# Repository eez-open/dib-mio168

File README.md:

### Ownership and License
The contributors are listed in CONTRIB.TXT.

Licenses | OSHWA UID
--|--
 | 

### Overview

The [EEZ DIB](https://github.com/eez-open/modular-psu) MIO168 module features multiple digital I/O, analog outputs and expansion connectors for carry various AFEs.

### Feature list

* On-board [STM32F446ZCT6](https://www.st.com/content/st_com/en/products/microcontrollers-microprocessors/stm32-32-bit-arm-cortex-mcus/stm32-high-performance-mcus/stm32f4-series/stm32f446/stm32f446zc.html) high-performance foundation line MCU, ARM Cortex-M4 with DSP and FPU, 256 KiB Flash, LQFP-144 package 
* 1 x 8-pin single row 3.81 mm connector (digital inputs)
* 1 x 16-pin dual row 3.81 mm I/O connector (digital and analog outputs)
* 2 x 10-pin ADIB 2.0 mm connectors
* 8 x protected digital inputs (3.3/5/24 V), 2 x fast/slow, 6 x slow
* 8 x digital outputs (low-side) with multiple protections, voltage clamp 42V, current limit 10 A
* 2 x PWM outputs (protected) or sensor bias power (+/-15 V, max. 10 mA)
* 2 x analog bipolar outputs (+/-5 V, +/-10 V, 0-5 V, 0-10 V). Voltage or current output with protection. 12-bit DAC, replaceable with pin compatible 14- or 16-bit version
* 2 x analog bipolar outputs +/-10 V. 12-bit DAC, replaceable with pin compatible 14- or 16-bit version
* On-board isolated power supply with +/-5.3 V outputs (with 4x multipliers), +/-15 V and +3.3 V LDO
* Firmware download via SPI
* Optional SWD for debugging
* I2C EEPROM for storing board specific parameters
* Dimensions: 146 x 95 mm, 4-layer PCB

### r3B1 prototype 3D model (without AFE installed)

### Firmware repository

https://github.com/eez-open/dib-mio168-fw  
The firmware download procedure is described in [Chapter 13.2](https://www.envox.eu/eez-bench-box-3/bb3-user-manual/13-firmware-upgrade/#bb3_man_module_upgrade) of the User Manual.  
The MIO168 module GUI is described in [Chapter 19](https://www.envox.eu/eez-bench-box-3/bb3-user-manual/19-mio168-mixed-input-output-module/) of the User Manual. 

### KiCad project (v7 or newer)

* [MIO168 r3B1](https://github.com/eez-open/dib-mio168/tree/master/EDA%20files/KiCad)

All symbols, footprints and 3D models used in the project can be found in the [EEZ-DIB Library](https://github.com/eez-open/eez-kicad-libraries) plugin for KiCad.

### Bill of materials

* [Download](https://github.com/eez-open/dib-mio168/tree/master/EDA%20files/KiCad/bom/ibom.html) as raw file _Interactive BOM_ (ibom.html) and open it locally in your browser.

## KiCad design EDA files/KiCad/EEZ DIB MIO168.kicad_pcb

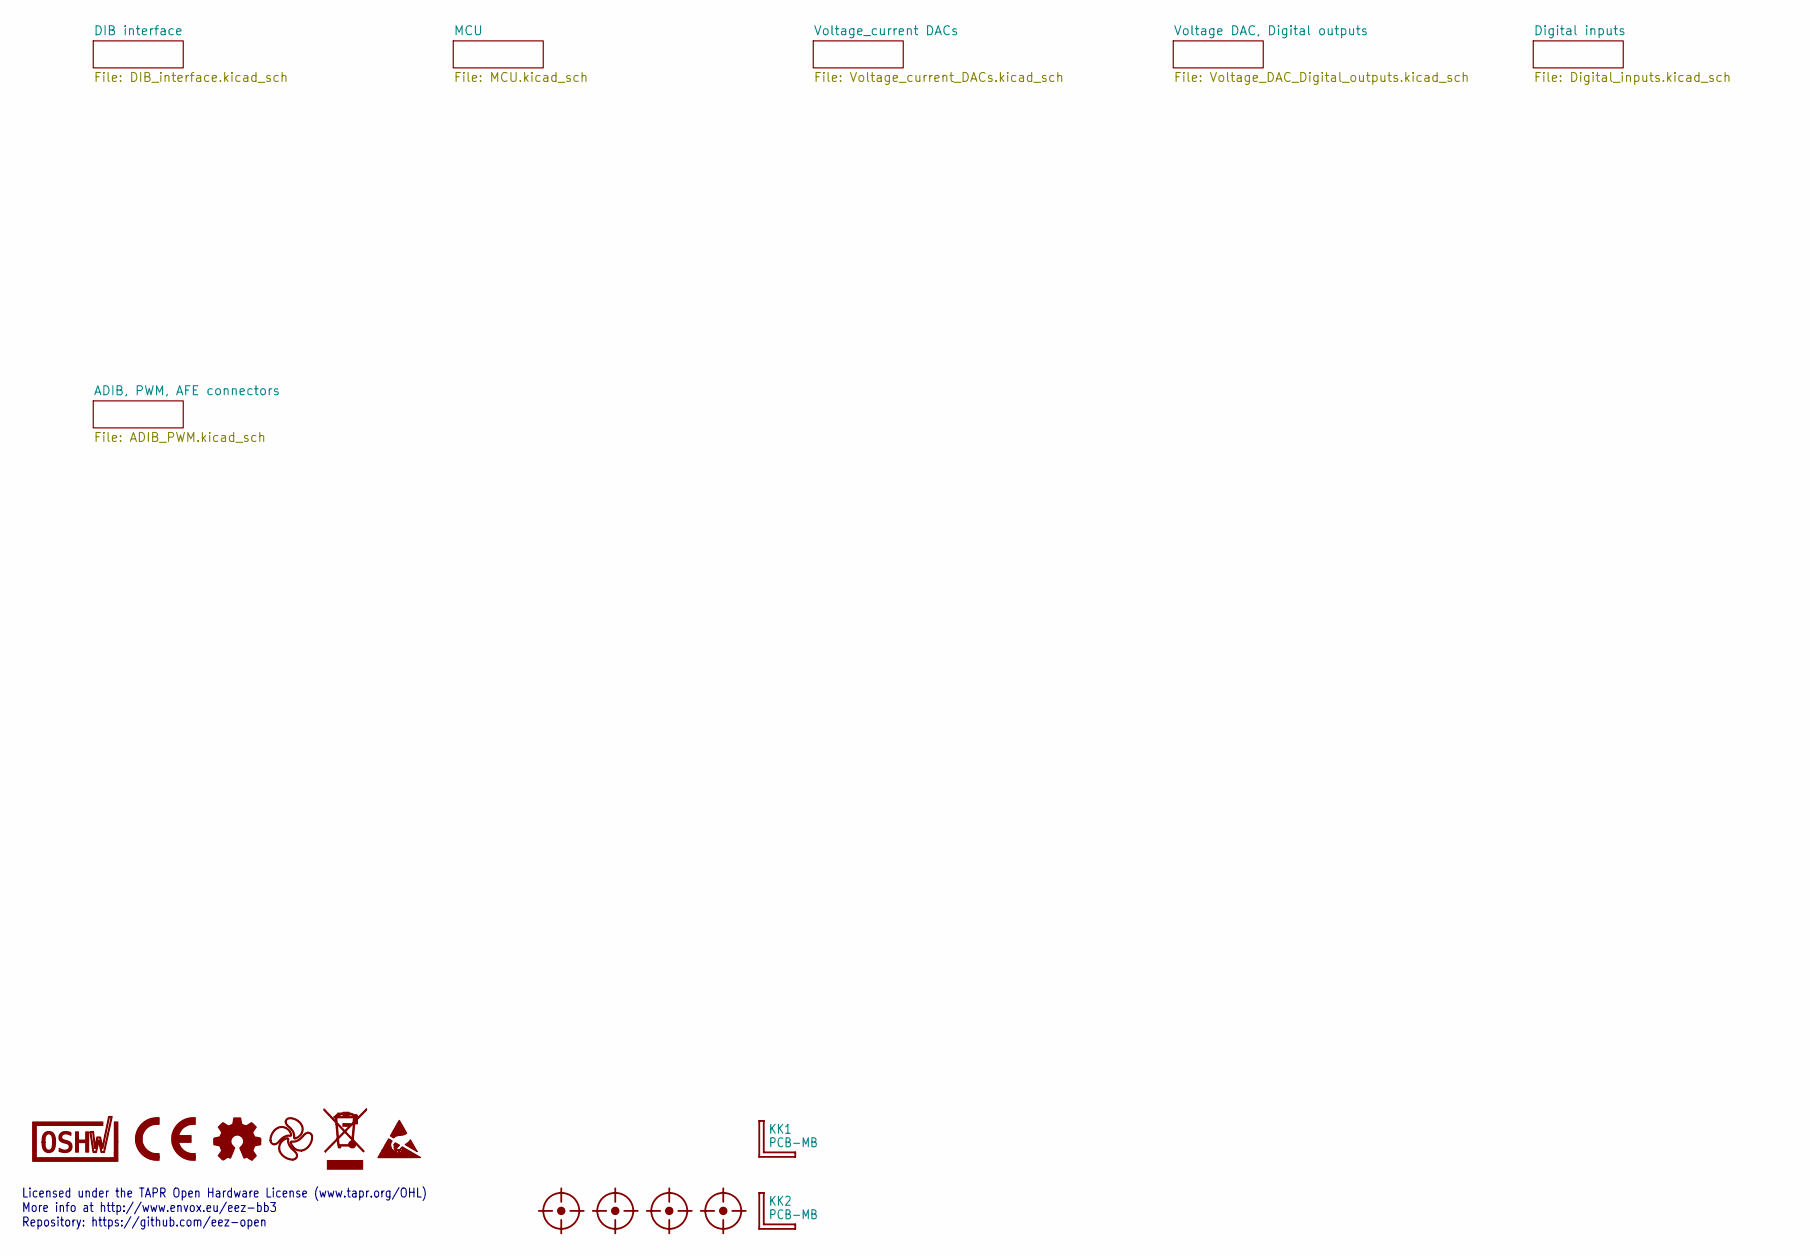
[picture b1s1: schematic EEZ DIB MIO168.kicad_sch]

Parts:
FM1, FM2, FM3, FM4: FIDUCIAL_2; Fiducial
KK1, KK2: PCB-MB; PCB-MB-01; DigiKey RPC1760-ND
LOGO1: OSHWA logo; OSHWA logo (9.5 x 5 mm)
LOGO2: CR logo; CE logo
LOGO3: Open HW logo
LOGO4: EEZ logo; EEZ logo (outline 6mm)
LOGO5: WEEE logo
LOGO6: ESD logo

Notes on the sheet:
Licensed under the TAPR Open Hardware License (www.tapr.org/OHL) More info at http://www.envox.eu/eez-bb3 Repository: https://github.com/eez-open

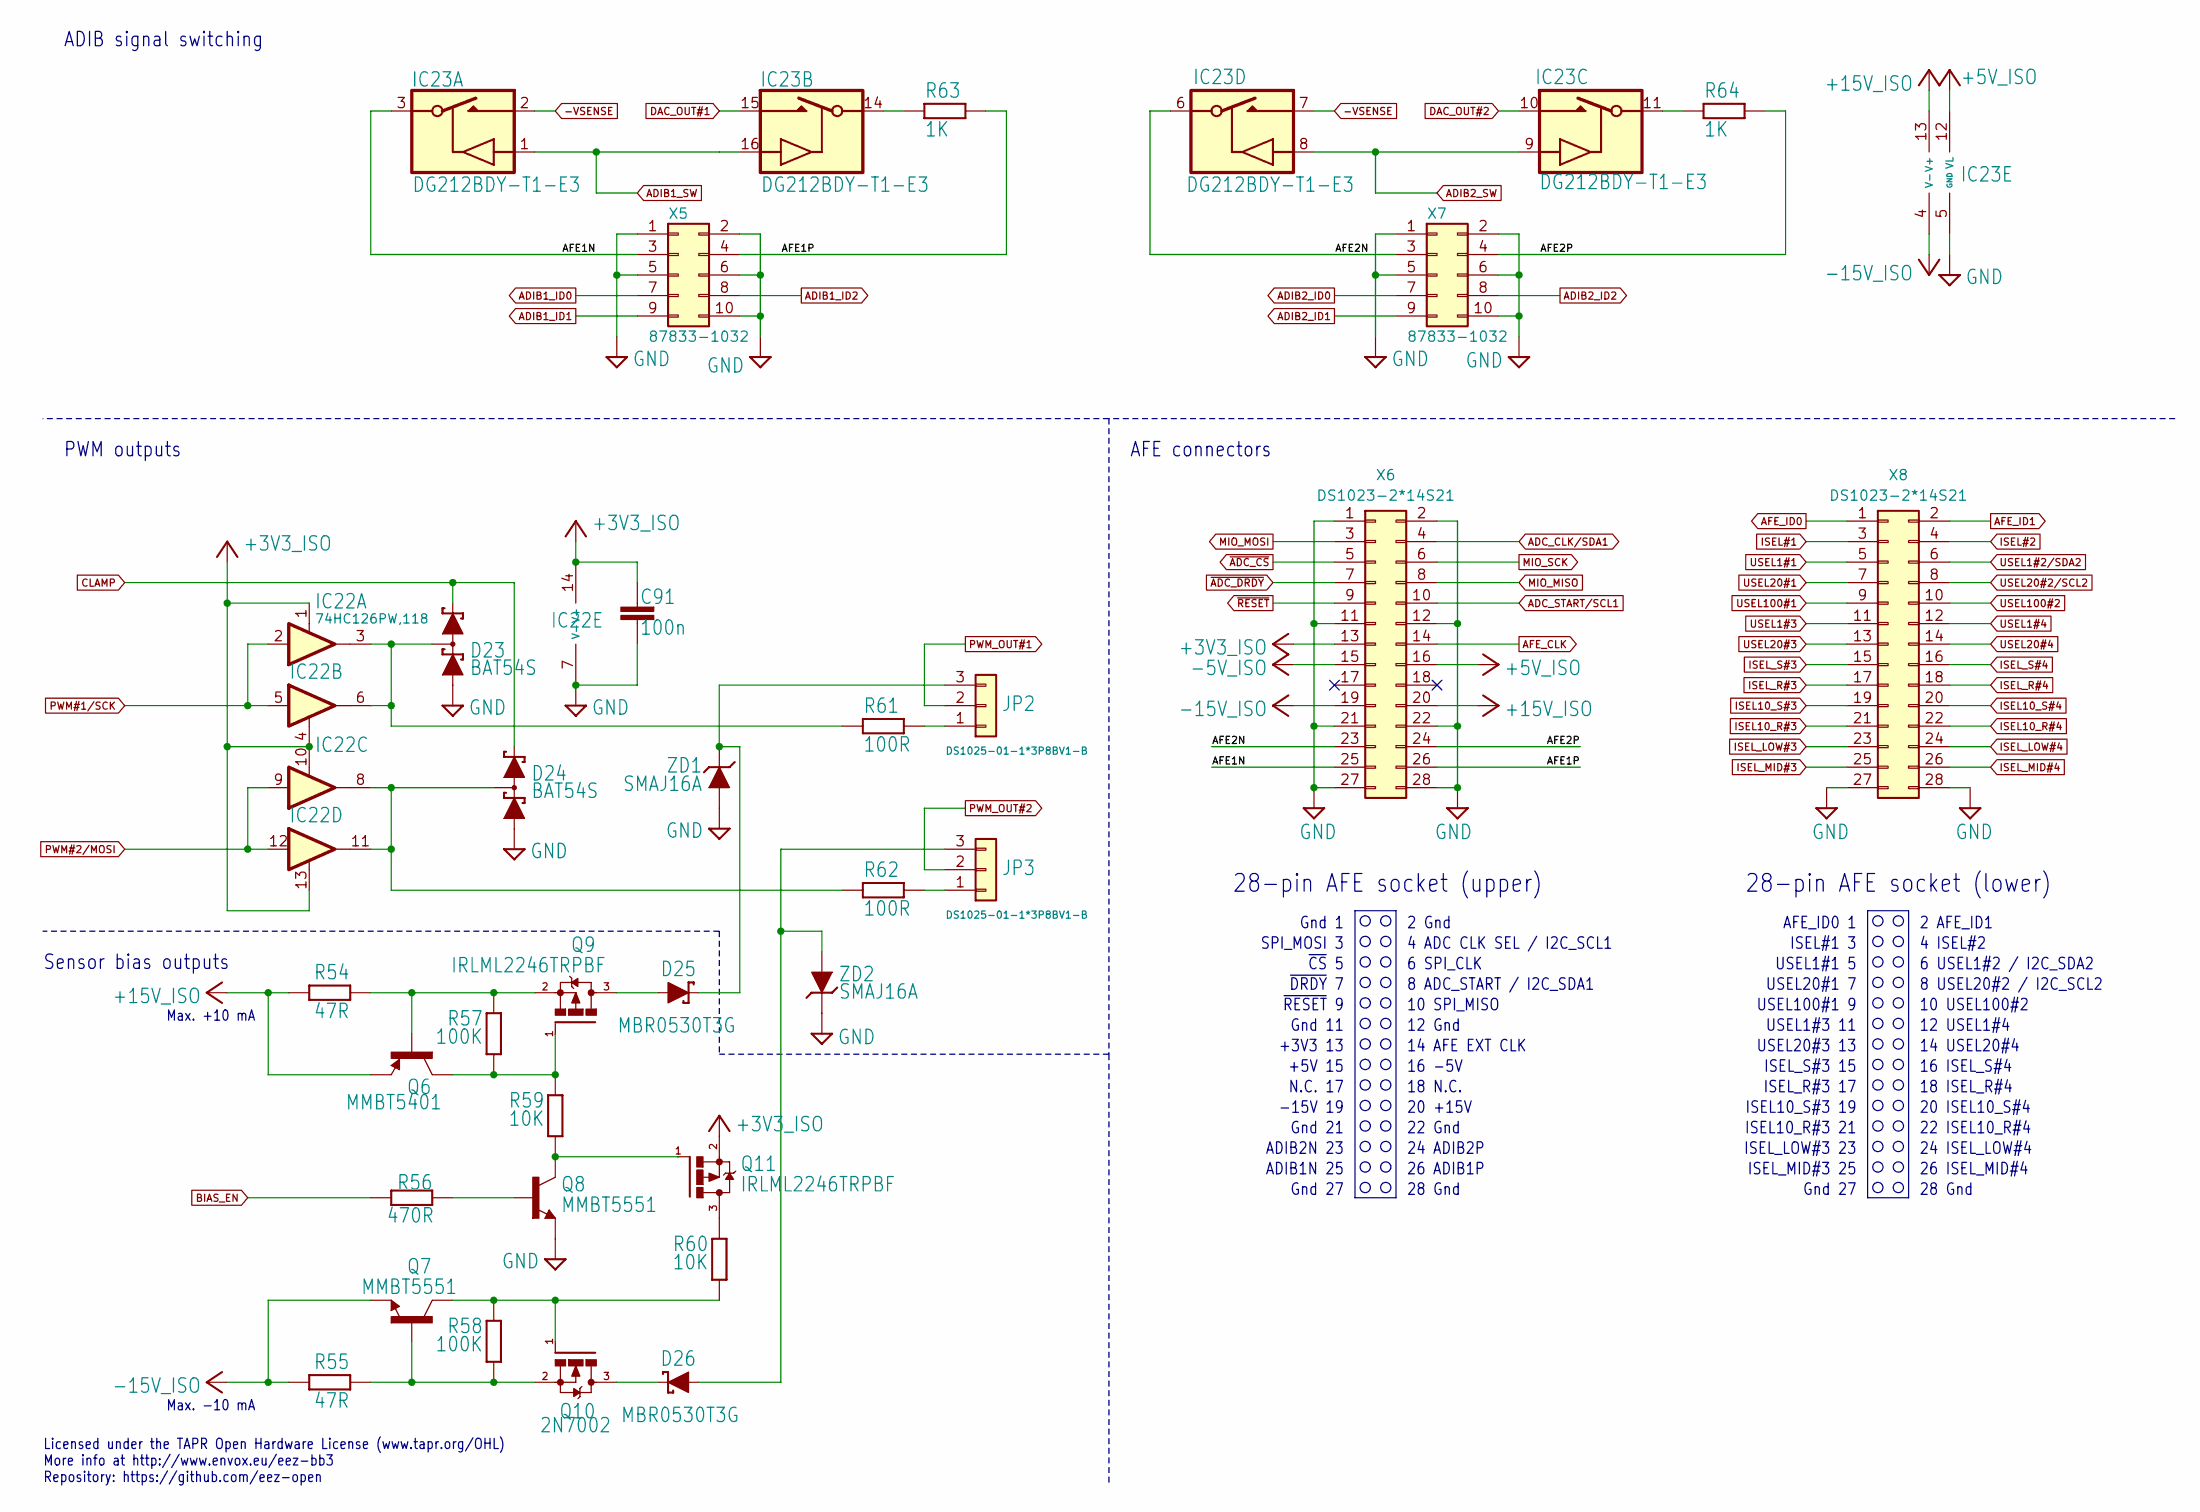
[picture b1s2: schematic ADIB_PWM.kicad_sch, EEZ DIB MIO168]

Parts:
C91: 100n; C_0603_1608Metric; DigiKey 1276-1005-2-ND
D23, D24: BAT54S; SOT23-3; DigiKey 497-2522-1-ND
D25, D26: MBR0530T3G; SOD123; DigiKey 863-MBR0530T3G
IC22: 74HC126PW,118; PW(R-PDSO-G14); DigiKey 1727-6579-1-ND
IC23: DG212BDY-T1-E3; SO16; DigiKey DG212BDY-T1-E3CT-ND
JP2, JP3: DS1025-01-1*3P8BV1-B; ZL303-03P; DigiKey 952-1312-ND
Q6: MMBT5401; SOT23-BEC; DigiKey MMBT5401-FDICT-ND
Q7, Q8: MMBT5551; SOT23-BEC; DigiKey MMBT5551LT1GOSCT-ND
Q9, Q11: IRLML2246TRPBF; SOT103P240X110-3N; DigiKey IRLML2246TRPBFTR-ND
Q10: 2N7002; SOT103P240X110-3N; DigiKey 2N7002LT1GOSCT-ND
R54, R55: 47R; R_0805_2012Metric; DigiKey P47.0CCT-ND
R56: 470R; R_0805_2012Metric; DigiKey 311-470CRCT-ND
R57, R58: 100K; R_0805_2012Metric; DigiKey RMCF0805FT100KCT-ND
R59, R60: 10K; R_0805_2012Metric; DigiKey CRGH0603F10K
R61, R62: 100R; R_0805_2012Metric; DigiKey 311-100CRCT-ND
R63, R64: 1K; R_0805_2012Metric; DigiKey RC0805FR-071KL
X5, X7: 87833-1032; DS1014-10RF1B; DigiKey WM8615-ND
X6, X8: DS1023-2*14S21; TSW-114-07-F-D; DigiKey SAM1183-14-ND
ZD1, ZD2: SMAJ16A; DO214AC-2; DigiKey SMAJ16A-FDICT-ND

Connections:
+3V3_ISO: C91.2, IC22.1 (EN), IC22.4 (EN), IC22.10 (EN), IC22.13 (EN), IC22.14 (V+), Q11.2 (S), X6.13; also elsewhere on the board
+5V_ISO: IC23.12 (VL), X6.16; also elsewhere on the board
+15V_ISO: IC23.13 (V+), Q6.E, R54.1, X6.20; also elsewhere on the board
-5V_ISO: X6.15; also elsewhere on the board
-15V_ISO: IC23.4 (V-), Q7.E, R55.1, X6.19; also elsewhere on the board
-VSENSE: IC23.2 (D), IC23.7 (D); also elsewhere on the board
/ADIB, PWM, AFE connectors/AFE1N: IC23.3 (S), X5.3, X6.25
/ADIB, PWM, AFE connectors/AFE1P: R63.1, X5.4, X6.26
/ADIB, PWM, AFE connectors/AFE2N: IC23.6 (S), X6.23, X7.3
/ADIB, PWM, AFE connectors/AFE2P: R64.1, X6.24, X7.4
ADC_CLK/SDA1: X6.4; also elsewhere on the board
ADC_START/SCL1: X6.10; also elsewhere on the board
ADIB1_ID0: X5.7; also elsewhere on the board
ADIB1_ID1: X5.9; also elsewhere on the board
ADIB1_ID2: X5.8; also elsewhere on the board
ADIB1_SW: IC23.1 (IN), IC23.16 (IN); also elsewhere on the board
ADIB2_ID0: X7.7; also elsewhere on the board
ADIB2_ID1: X7.9; also elsewhere on the board
ADIB2_ID2: X7.8; also elsewhere on the board
ADIB2_SW: IC23.8 (IN), IC23.9 (IN); also elsewhere on the board
AFE_CLK: X6.14; also elsewhere on the board
AFE_ID0: X8.1; also elsewhere on the board
AFE_ID1: X8.2; also elsewhere on the board
BIAS_EN: R56.1; also elsewhere on the board
CLAMP: D23.2 (C2), D24.2 (C2); also elsewhere on the board
DAC_OUT#1: IC23.15 (D); also elsewhere on the board
DAC_OUT#2: IC23.10 (D); also elsewhere on the board
GND: C91.1, D23.1 (A1), D24.1 (A1), IC22.7 (V-), IC23.5 (GND), Q8.E, X5.1, X5.2, X5.5, X5.6, X5.10, X6.1, X6.2, X6.11, X6.12, X6.21, X6.22, X6.27, X6.28, X7.1, X7.2, X7.5, X7.6, X7.10, X8.27, X8.28, ZD1.C, ZD2.A; also elsewhere on the board
ISEL10_R#3: X8.21; also elsewhere on the board
ISEL10_R#4: X8.22; also elsewhere on the board
ISEL10_S#3: X8.19; also elsewhere on the board
ISEL10_S#4: X8.20; also elsewhere on the board
ISEL#1: X8.3; also elsewhere on the board
ISEL#2: X8.4; also elsewhere on the board
ISEL_LOW#3: X8.23; also elsewhere on the board
ISEL_LOW#4: X8.24; also elsewhere on the board
ISEL_MID#3: X8.25; also elsewhere on the board
ISEL_MID#4: X8.26; also elsewhere on the board
ISEL_R#3: X8.17; also elsewhere on the board
ISEL_R#4: X8.18; also elsewhere on the board
ISEL_S#3: X8.15; also elsewhere on the board
ISEL_S#4: X8.16; also elsewhere on the board
MIO_MISO: X6.8; also elsewhere on the board
MIO_MOSI: X6.3; also elsewhere on the board
MIO_SCK: X6.6; also elsewhere on the board
unnamed: D23.3 (C1A2), IC22.3 (O), IC22.6 (O), R61.2
unnamed: D24.3 (C1A2), IC22.8 (O), IC22.11 (O), R62.2
unnamed: IC23.14 (S), R63.2
unnamed: IC23.11 (S), R64.2
unnamed: JP2.1, R61.1
unnamed: D25.C, JP2.3, ZD1.A
unnamed: JP3.1, R62.1
unnamed: D26.A, JP3.3, ZD2.C
unnamed: Q8.B, R56.2
unnamed: D25.A, Q9.3 (D)
unnamed: Q6.C, Q9.1 (G), R57.2, R59.1
unnamed: Q6.B, Q9.2 (S), R54.2, R57.1
unnamed: D26.C, Q10.3 (D)
unnamed: Q7.C, Q10.1 (G), R58.1, R60.2
unnamed: Q7.B, Q10.2 (S), R55.2, R58.2
unnamed: Q11.3 (D), R60.1
unnamed: Q8.C, Q11.1 (G), R59.2
PWM#1/SCK: IC22.2 (I), IC22.5 (I); also elsewhere on the board
PWM#2/MOSI: IC22.9 (I), IC22.12 (I); also elsewhere on the board
PWM_OUT#1: JP2.2; also elsewhere on the board
PWM_OUT#2: JP3.2; also elsewhere on the board
USEL1#1: X8.5; also elsewhere on the board
USEL1#2/SDA2: X8.6; also elsewhere on the board
USEL1#3: X8.11; also elsewhere on the board
USEL1#4: X8.12; also elsewhere on the board
USEL20#1: X8.7; also elsewhere on the board
USEL20#2/SCL2: X8.8; also elsewhere on the board
USEL20#3: X8.13; also elsewhere on the board
USEL20#4: X8.14; also elsewhere on the board
USEL100#1: X8.9; also elsewhere on the board
USEL100#2: X8.10; also elsewhere on the board
~ADC_CS: X6.5; also elsewhere on the board
~ADC_DRDY: X6.7; also elsewhere on the board
~RESET: X6.9; also elsewhere on the board

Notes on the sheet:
8 ADC_START / I2C_SDA1
~{CS} 5
28-pin AFE socket (upper)
22 ISEL10_R#4
ISEL#1 3
USEL100#1 9
N.C. 17
12 USEL1#4
ADIB2N 23
ISEL_S#3 15
4 ADC CLK SEL / I2C_SCL1
28 Gnd
22 Gnd
6 SPI_CLK
Gnd 11
8 USEL20#2 / I2C_SCL2
24 ISEL_LOW#4
AFE_ID0 1
Gnd 1
26 ADIB1P
AFE connectors
~{RESET} 9
12 Gnd
ISEL_MID#3 25
+5V 15
18 ISEL_R#4
Gnd 27
Licensed under the TAPR Open Hardware License (www.tapr.org/OHL) More info at http://www.envox.eu/eez-bb3 Repository: https://github.com/eez-open
Max. -10 mA
24 ADIB2P
28-pin AFE socket (lower)
4 ISEL#2
2 Gnd
6 USEL1#2 / I2C_SDA2
Max. +10 mA
+3V3 13
10 USEL100#2
26 ISEL_MID#4
Sensor bias outputs
18 N.C.

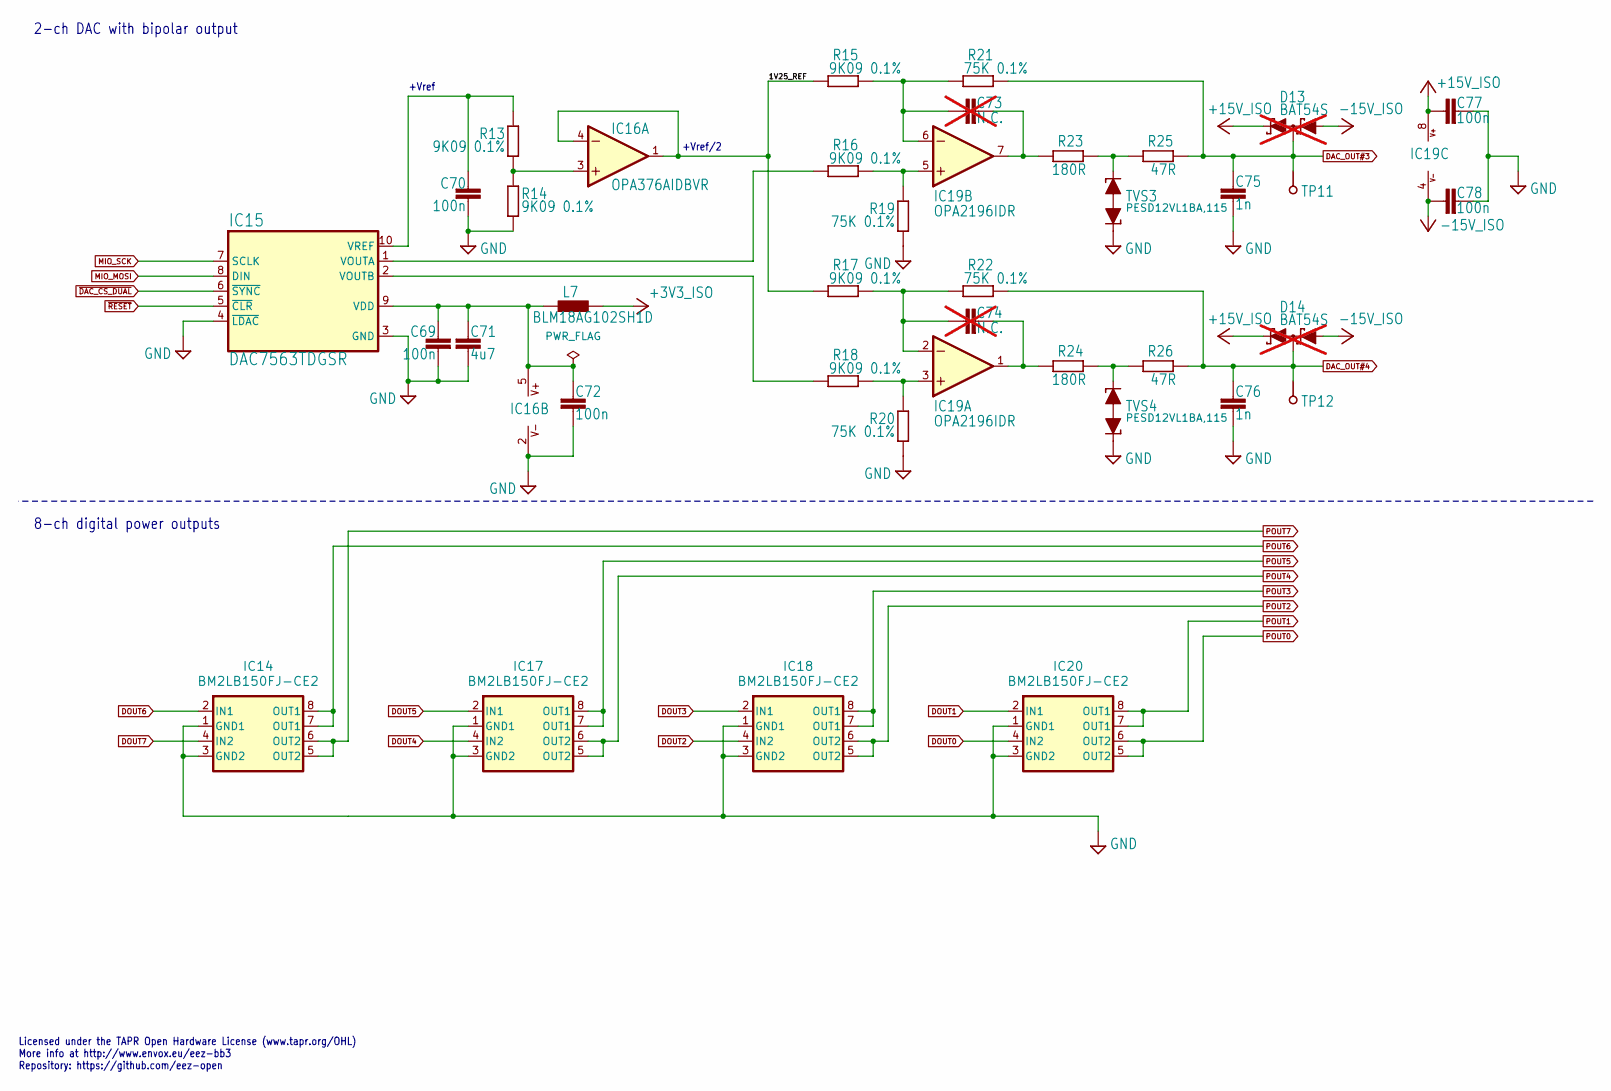
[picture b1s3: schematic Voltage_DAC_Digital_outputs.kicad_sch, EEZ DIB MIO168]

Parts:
C69, C70, C72, C77, C78: 100n; C_0603_1608Metric; DigiKey 1276-1005-2-ND
C71: 4u7; C_0805_2012Metric; DigiKey 490-14466-1-ND
C73, C74: N.C.; C_0805_2012Metric; not fitted
C75, C76: 1n; C_0805_2012Metric; DigiKey 732-7858-1-ND
D13, D14: BAT54S; SOT23-3; DigiKey 497-2522-1-ND; not fitted
IC14, IC17, IC18, IC20: BM2LB150FJ-CE2; SOIC127P600X173-8N; DigiKey BM2LB150FJ-CE2TR-ND
IC15: DAC7563TDGSR; DGS10; DigiKey 296-43287-1-ND
IC16: OPA376AIDBVR; SOT23-5L_STM; DigiKey 296-39130-2-ND
IC19: OPA2196IDR; SOIC127P600X173-8N; DigiKey 296-1282-1-ND
L7: BLM18AG102SH1D; BEAD0603; DigiKey 490-7809-1-ND
R13, R14, R15, R16, R17, R18: 9K09 0.1%; R_0805_2012Metric; DigiKey P9.09KDACT-ND
R19, R20, R21, R22: 75K 0.1%; R_0805_2012Metric; DigiKey P75KDACT-ND
R23, R24: 180R; R_0805_2012Metric; DigiKey A126343CT-ND
R25, R26: 47R; R_0805_2012Metric; DigiKey P47.0CCT-ND
TP11, TP12: PCB_TEST_TABSHIELD; Testhole 24_50mils
TVS3, TVS4: PESD12VL1BA,115; SOD-323_PESD; DigiKey 1727-3808-1-ND

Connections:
+3V3_ISO: L7.2; also elsewhere on the board
+15V_ISO: C77.1, D13.2 (C2), D14.2 (C2), IC19.8 (V+); also elsewhere on the board
-15V_ISO: C78.1, D13.1 (A1), D14.1 (A1), IC19.4 (V-); also elsewhere on the board
/Voltage DAC, Digital outputs/1V25_REF: IC16.1 (OUT), IC16.4 (-IN), R15.2, R17.2
DAC_OUT#3: C75.1, D13.3 (C1A2), R21.1, R25.2, TP11.1; also elsewhere on the board
DAC_OUT#4: C76.1, D14.3 (C1A2), R22.1, R26.2, TP12.1; also elsewhere on the board
DOUT0: IC20.4 (IN2); also elsewhere on the board
DOUT1: IC20.2 (IN1); also elsewhere on the board
DOUT2: IC18.4 (IN2); also elsewhere on the board
DOUT3: IC18.2 (IN1); also elsewhere on the board
DOUT4: IC17.4 (IN2); also elsewhere on the board
DOUT5: IC17.2 (IN1); also elsewhere on the board
DOUT6: IC14.2 (IN1); also elsewhere on the board
DOUT7: IC14.4 (IN2); also elsewhere on the board
GND: C69.2, C70.1, C71.1, C72.2, C75.2, C76.2, C77.2, C78.2, IC14.1 (GND1), IC14.3 (GND2), IC15.3 (GND), IC15.4 (~LDAC), IC16.2 (V-), IC17.1 (GND1), IC17.3 (GND2), IC18.1 (GND1), IC18.3 (GND2), IC20.1 (GND1), IC20.3 (GND2), R14.2, R19.2, R20.2, TVS3.C1 (1), TVS4.C1 (1); also elsewhere on the board
MIO_MOSI: IC15.8 (DIN); also elsewhere on the board
MIO_SCK: IC15.7 (SCLK); also elsewhere on the board
unnamed: C69.1, C71.2, C72.1, IC15.9 (VDD), IC16.5 (V+), L7.1
unnamed: IC15.1 (VOUTA), R16.2
unnamed: IC15.2 (VOUTB), R18.2
unnamed: C70.2, IC15.10 (VREF), R13.1
unnamed: IC16.3 (+IN), R13.2, R14.1
unnamed: IC19.3 (+IN), R18.1, R20.1
unnamed: C74.1, IC19.2 (-IN), R17.1, R22.2
unnamed: C74.2, IC19.1 (OUT), R24.1
unnamed: IC19.5 (+IN), R16.1, R19.1
unnamed: C73.1, IC19.6 (-IN), R15.1, R21.2
unnamed: C73.2, IC19.7 (OUT), R23.1
unnamed: R23.2, R25.1, TVS3.C2 (2)
unnamed: R24.2, R26.1, TVS4.C2 (2)
POUT0: IC20.5 (OUT2), IC20.6 (OUT2); also elsewhere on the board
POUT1: IC20.7 (OUT1), IC20.8 (OUT1); also elsewhere on the board
POUT2: IC18.5 (OUT2), IC18.6 (OUT2); also elsewhere on the board
POUT3: IC18.7 (OUT1), IC18.8 (OUT1); also elsewhere on the board
POUT4: IC17.5 (OUT2), IC17.6 (OUT2); also elsewhere on the board
POUT5: IC17.7 (OUT1), IC17.8 (OUT1); also elsewhere on the board
POUT6: IC14.7 (OUT1), IC14.8 (OUT1); also elsewhere on the board
POUT7: IC14.5 (OUT2), IC14.6 (OUT2); also elsewhere on the board
~DAC_CS_DUAL: IC15.6 (~SYNC); also elsewhere on the board
~RESET: IC15.5 (~CLR); also elsewhere on the board

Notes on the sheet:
+Vref
+Vref/2
8-ch digital power outputs
2-ch DAC with bipolar output
Licensed under the TAPR Open Hardware License (www.tapr.org/OHL) More info at http://www.envox.eu/eez-bb3 Repository: https://github.com/eez-open

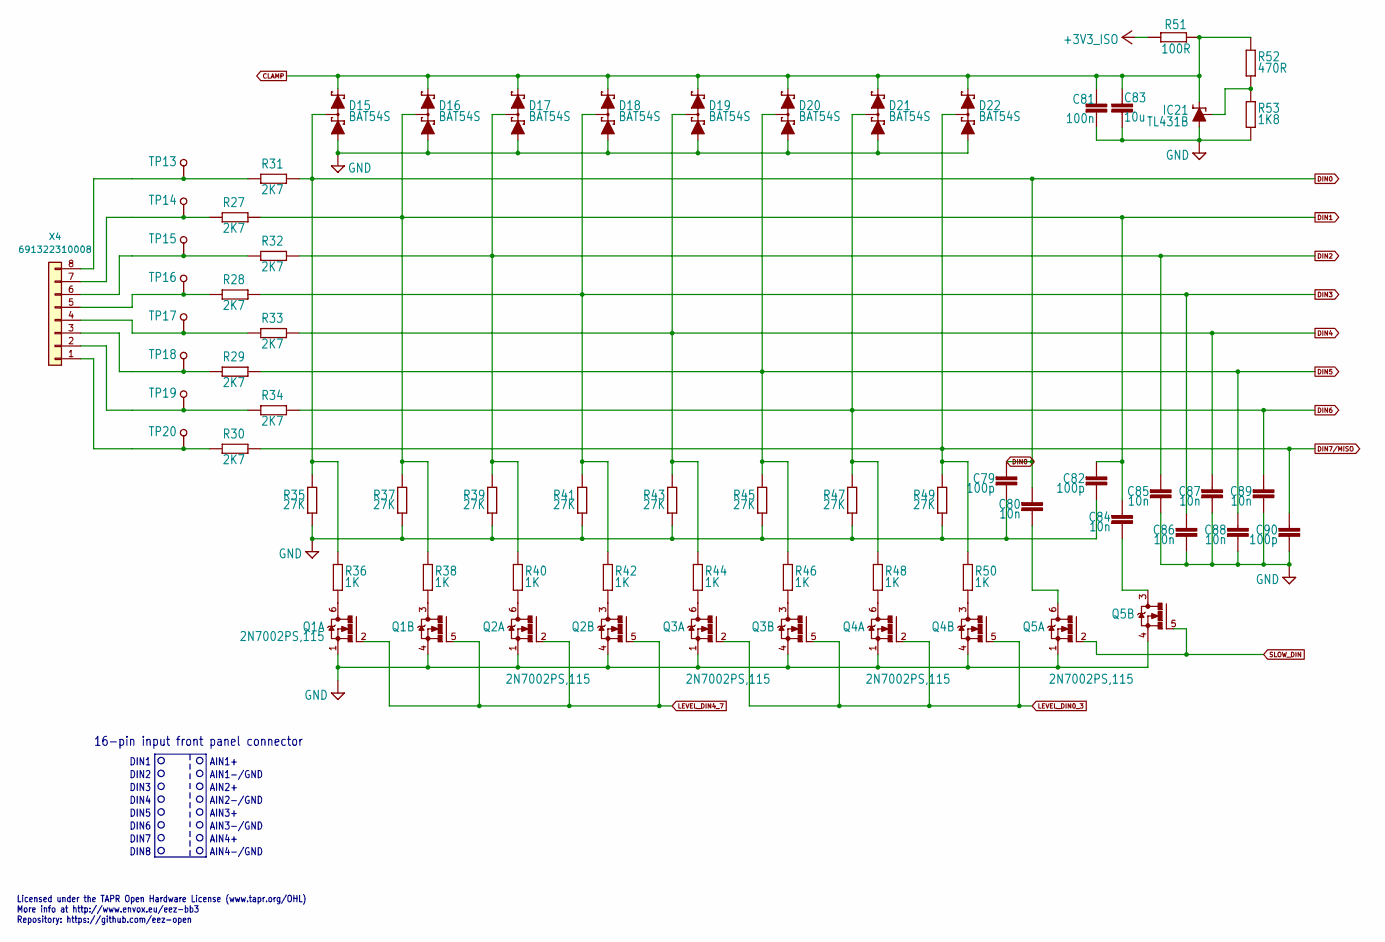
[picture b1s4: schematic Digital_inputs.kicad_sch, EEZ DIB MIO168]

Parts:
C79, C82, C90: 100p; C_0805_2012Metric; DigiKey 399-15000-1-ND
C80, C84, C85, C86, C87, C88, C89: 10n; C_0805_2012Metric; DigiKey 490-7194-1-ND
C81: 100n; C_0603_1608Metric; DigiKey 1276-1005-2-ND
C83: 10u; C_1206_3216Metric; DigiKey 1276-2872-1-ND
D15, D16, D17, D18, D19, D20, D21, D22: BAT54S; SOT23-3; DigiKey 497-2522-1-ND
IC21: TL431B; SOT103P240X110-3N; DigiKey 296-17332-1-ND
Q1, Q2, Q3, Q4, Q5: 2N7002PS,115; SC88; DigiKey 1727-4791-2-ND
R27, R28, R29, R30, R31, R32, R33, R34: 2K7; R_1206_3216Metric; DigiKey 311-2.70KFRCT-ND
R35, R37, R39, R41, R43, R45, R47, R49: 27K; R_0805_2012Metric; DigiKey A126356CT-ND
R36, R38, R40, R42, R44, R46, R48, R50: 1K; R_0805_2012Metric; DigiKey RC0805FR-071KL
R51: 100R; R_0805_2012Metric; DigiKey 311-100CRCT-ND
R52: 470R; R_0805_2012Metric; DigiKey 311-470CRCT-ND
R53: 1K8; R_0805_2012Metric; DigiKey A129752CT-ND
TP13, TP14, TP15, TP16, TP17, TP18, TP19, TP20: PCB_TEST_TABSHIELD; Testhole 24_50mils
X4: 691322310008; DigiKey 732-2093-ND

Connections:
+3V3_ISO: R51.1; also elsewhere on the board
CLAMP: C81.1, C83.1, D15.2 (C2), D16.2 (C2), D17.2 (C2), D18.2 (C2), D19.2 (C2), D20.2 (C2), D21.2 (C2), D22.2 (C2), IC21.1 (C), R51.2, R52.1; also elsewhere on the board
DIN0: C79.1, C80.1, D15.3 (C1A2), R31.2, R35.2, R36.1; also elsewhere on the board
DIN1: C82.1, C84.1, D16.3 (C1A2), R27.2, R37.2, R38.1; also elsewhere on the board
DIN2: C85.1, D17.3 (C1A2), R32.2, R39.2, R40.1; also elsewhere on the board
DIN3: C86.1, D18.3 (C1A2), R28.2, R41.2, R42.1; also elsewhere on the board
DIN4: C87.1, D19.3 (C1A2), R33.2, R43.2, R44.1; also elsewhere on the board
DIN5: C88.1, D20.3 (C1A2), R29.2, R45.2, R46.1; also elsewhere on the board
DIN6: C89.1, D21.3 (C1A2), R34.2, R47.2, R48.1; also elsewhere on the board
DIN7/MISO: C90.1, D22.3 (C1A2), R30.2, R49.2, R50.1; also elsewhere on the board
GND: C79.2, C81.2, C82.2, C83.2, C85.2, C86.2, C87.2, C88.2, C89.2, C90.2, D15.1 (A1), D16.1 (A1), D17.1 (A1), D18.1 (A1), D19.1 (A1), D20.1 (A1), D21.1 (A1), D22.1 (A1), IC21.3 (A), Q1.1 (S), Q1.4 (S), Q2.1 (S), Q2.4 (S), Q3.1 (S), Q3.4 (S), Q4.1 (S), Q4.4 (S), Q5.1 (S), Q5.4 (S), R35.1, R37.1, R39.1, R41.1, R43.1, R45.1, R47.1, R49.1, R53.2; also elsewhere on the board
LEVEL_DIN0_3: Q3.2 (G), Q3.5 (G), Q4.2 (G), Q4.5 (G); also elsewhere on the board
LEVEL_DIN4_7: Q1.2 (G), Q1.5 (G), Q2.2 (G), Q2.5 (G); also elsewhere on the board
unnamed: IC21.2 (R), R52.2, R53.1
unnamed: Q1.6 (D), R36.2
unnamed: Q1.3 (D), R38.2
unnamed: Q2.6 (D), R40.2
unnamed: Q2.3 (D), R42.2
unnamed: Q3.6 (D), R44.2
unnamed: Q3.3 (D), R46.2
unnamed: Q4.6 (D), R48.2
unnamed: Q4.3 (D), R50.2
unnamed: C80.2, Q5.6 (D)
unnamed: C84.2, Q5.3 (D)
unnamed: R31.1, TP13.1, X4.8
unnamed: R27.1, TP14.1, X4.7
unnamed: R32.1, TP15.1, X4.6
unnamed: R28.1, TP16.1, X4.5
unnamed: R33.1, TP17.1, X4.4
unnamed: R29.1, TP18.1, X4.3
unnamed: R34.1, TP19.1, X4.2
unnamed: R30.1, TP20.1, X4.1
SLOW_DIN: Q5.2 (G), Q5.5 (G); also elsewhere on the board

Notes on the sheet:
DIN4
Licensed under the TAPR Open Hardware License (www.tapr.org/OHL) More info at http://www.envox.eu/eez-bb3 Repository: https://github.com/eez-open
AIN1-/GND
DIN6
AIN3+
AIN3-/GND
DIN2
DIN3
AIN1+
AIN4-/GND
DIN7
16-pin input front panel connector
AIN2+
AIN4+
DIN8
DIN5
AIN2-/GND
DIN1

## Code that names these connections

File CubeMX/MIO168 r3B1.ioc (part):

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Mcu.Name=STM32F446Z(C-E)Tx
Mcu.Package=LQFP144
Mcu.UserName=STM32F446ZCTx
PA0-WKUP.GPIOParameters=GPIO_Speed,GPIO_Label
PA0-WKUP.GPIO_Label=DOUT0
PA0-WKUP.GPIO_Speed=GPIO_SPEED_FREQ_LOW
PA0-WKUP.Signal=GPIO_Output
PA1.GPIOParameters=GPIO_Label
PA1.GPIO_Label=DOUT1
PA1.Signal=GPIO_Output
PA10.GPIOParameters=GPIO_Label
PA10.GPIO_Label=ADIB2_SW
PA10.Signal=GPIO_Output
PA11.GPIOParameters=GPIO_Label
PA11.GPIO_Label=ISEL_LOW\#4
PA11.Signal=GPIO_Output
PA12.GPIOParameters=GPIO_Label
PA12.GPIO_Label=ISEL_MID\#4
PA12.Signal=GPIO_Output
PA13.Mode=Serial_Wire
PA13.Signal=SYS_JTMS-SWDIO
PA14.Mode=Serial_Wire
PA14.Signal=SYS_JTCK-SWCLK
PA15.GPIOParameters=GPIO_Speed,PinState,GPIO_Label
PA15.GPIO_Label=USEL100\#2
PA15.GPIO_Speed=GPIO_SPEED_FREQ_LOW
PA15.PinState=GPIO_PIN_SET
PA15.Signal=GPIO_Output
PA2.GPIOParameters=GPIO_Label
PA2.GPIO_Label=DOUT2
PA2.Signal=GPIO_Output
PA3.GPIOParameters=GPIO_Label
PA3.GPIO_Label=DOUT3
PA3.Signal=GPIO_Output
PA4.GPIOParameters=GPIO_Label
PA4.GPIO_Label=SLOW_DIN
PA4.Signal=GPIO_Output
PA5.GPIOParameters=GPIO_Label
PA5.GPIO_Label=PWM1
PA5.Signal=S_TIM2_CH1_ETR
PA6.GPIOParameters=GPIO_Label
PA6.GPIO_Label=DIN7
PA6.Signal=GPIO_Input
PA7.GPIOParameters=GPIO_Label
PA7.GPIO_Label=PWM2
PA7.Signal=S_TIM3_CH2
PA8.GPIOParameters=GPIO_Label
PA8.GPIO_Label=ISEL10_S\#4
PA8.Signal=GPIO_Output
PA9.GPIOParameters=GPIO_Label
PA9.GPIO_Label=ISEL10_R\#4
PA9.Signal=GPIO_Output
PB0.GPIOParameters=GPIO_Label
PB0.GPIO_Label=DOUT6
PB0.Signal=GPIO_Output
PB1.GPIOParameters=GPIO_Label
PB1.GPIO_Label=DOUT7
PB1.Signal=GPIO_Output
PB10.GPIOParameters=GPIO_Label
PB10.GPIO_Label=USEL20\#2
PB10.Signal=GPIO_Output
PB11.GPIOParameters=GPIO_Label
PB11.GPIO_Label=USEL1\#2
PB11.Signal=GPIO_Output
PB12.GPIOParameters=GPIO_Label
PB12.GPIO_Label=DIB_NSS
PB12.Mode=NSS_Signal_Hard_Input
PB12.Signal=SPI2_NSS
PB13.GPIOParameters=GPIO_Label
PB13.GPIO_Label=ADIB2_ID0
PB13.Signal=GPIO_Input
PB14.GPIOParameters=GPIO_Label
PB14.GPIO_Label=DIB_MISO
PB14.Mode=Full_Duplex_Slave
PB14.Signal=SPI2_MISO
PB15.GPIOParameters=GPIO_Label
PB15.GPIO_Label=DIB_MOSI
PB15.Mode=Full_Duplex_Slave
PB15.Signal=SPI2_MOSI
PB2.GPIOParameters=GPIO_Label
PB2.GPIO_Label=ADC_DRDY
PB2.Signal=GPIO_Input
PB3.GPIOParameters=GPIO_Label
PB3.GPIO_Label=MIO_SCK
PB3.Mode=Full_Duplex_Master
PB3.Signal=SPI3_SCK
PB4.GPIOParameters=GPIO_Label
PB4.GPIO_Label=MIO_MISO
PB4.Mode=Full_Duplex_Master
PB4.Signal=SPI3_MISO
PB5.GPIOParameters=GPIO_Label
PB5.GPIO_Label=MIO_MOSI
PB5.Mode=Full_Duplex_Master
PB5.Signal=SPI3_MOSI
PB6.GPIOParameters=GPIO_Label
PB6.GPIO_Label=ADC_START/SCL1
PB6.Signal=GPIO_Output
PB7.GPIOParameters=GPIO_Label
PB7.GPIO_Label=ADC_CLK/SDA1
PB7.Signal=GPIO_Output
PB8.GPIOParameters=GPIO_Label
PB8.GPIO_Label=LEVEL_DIN0_3
PB8.Signal=GPIO_Output
PB9.GPIOParameters=GPIO_Label
PB9.GPIO_Label=LEVEL_DIN3_7
PB9.Signal=GPIO_Output
PC0.Signal=FMC_SDNWE
PC1.GPIOParameters=GPIO_Label
PC1.GPIO_Label=ADIB2_ID1
PC1.Signal=GPIO_Input
PC10.GPIOParameters=GPIO_Label
PC10.GPIO_Label=USEL20\#3
PC10.Signal=GPIO_Output
PC11.GPIOParameters=GPIO_Label
PC11.GPIO_Label=USEL1\#3
PC11.Signal=GPIO_Output
PC12.GPIOParameters=GPIO_Label
PC12.GPIO_Label=DAC_ALARM
PC12.Signal=GPIO_Input
PC13.GPIOParameters=GPIO_Label
PC13.GPIO_Label=USEL1\#4
PC13.Signal=GPIO_Output
PC14-OSC32_IN.GPIOParameters=GPIO_Label
PC14-OSC32_IN.GPIO_Label=USEL20\#4
PC14-OSC32_IN.Signal=GPIO_Output
PC15-OSC32_OUT.GPIOParameters=GPIO_Label
PC15-OSC32_OUT.GPIO_Label=ISEL\#2
PC15-OSC32_OUT.Signal=GPIO_Output
PC2.Mode=SdramChipSelect1_1
PC2.Signal=FMC_SDNE0
PC3.Mode=SdramChipSelect1_1
PC3.Signal=FMC_SDCKE0
PC4.GPIOParameters=GPIO_Label
PC4.GPIO_Label=DOUT4
PC4.Signal=GPIO_Output
PC5.GPIOParameters=GPIO_Label
PC5.GPIO_Label=DOUT5
PC5.Signal=GPIO_Output
PC6.GPIOParameters=GPIO_Label
PC6.GPIO_Label=ISEL_R\#4
PC6.Signal=GPIO_Output
PC7.GPIOParameters=GPIO_Label
PC7.GPIO_Label=DIB_SCK
PC7.Mode=Full_Duplex_Slave
PC7.Signal=SPI2_SCK
PC8.GPIOParameters=GPIO_Label
PC8.GPIO_Label=ISEL_S\#4
PC8.Signal=GPIO_Output
PC9.GPIOParameters=GPIO_Label
PC9.GPIO_Label=AFE_CLK
PC9.Mode=Clock-out-2
PC9.Signal=RCC_MCO_2
PD0.Signal=FMC_D2_DA2
PD1.Signal=FMC_D3_DA3
PD10.Signal=FMC_D15_DA15
PD11.GPIOParameters=GPIO_PuPd,GPIO_Label
PD11.GPIO_Label=ADIB1_ID2
PD11.GPIO_PuPd=GPIO_PULLUP
PD11.Signal=GPIO_Input
PD12.GPIOParameters=GPIO_PuPd,GPIO_Label
PD12.GPIO_Label=ADIB1_ID1
PD12.GPIO_PuPd=GPIO_PULLUP
PD12.Signal=GPIO_Input
PD13.GPIOParameters=GPIO_PuPd,GPIO_Label
PD13.GPIO_Label=ADIB1_ID0
PD13.GPIO_PuPd=GPIO_PULLUP
PD13.Signal=GPIO_Input
PD14.Signal=FMC_D0_DA0
PD15.Signal=FMC_D1_DA1
PD2.GPIOParameters=GPIO_Label
PD2.GPIO_Label=BIAS_EN
PD2.Signal=GPIO_Output
PD3.GPIOParameters=GPIO_Label
PD3.GPIO_Label=ADIB1_SW
PD3.Signal=GPIO_Output
PD4.GPIOParameters=GPIO_Label
PD4.GPIO_Label=ISEL_MID\#3
PD4.Signal=GPIO_Output
PD5.GPIOParameters=GPIO_Label
PD5.GPIO_Label=ISEL_LOW\#3
PD5.Signal=GPIO_Output
PD6.GPIOParameters=GPIO_Label
PD6.GPIO_Label=ISEL10_R\#3
PD6.Signal=GPIO_Output
PD7.GPIOParameters=GPIO_Label
PD7.GPIO_Label=ISEL10_S\#3
PD7.Signal=GPIO_Output
PD8.Signal=FMC_D13_DA13
PD9.Signal=FMC_D14_DA14
PE0.Signal=FMC_NBL0
PE1.Signal=FMC_NBL1
PE10.Signal=FMC_D7_DA7
PE11.Signal=FMC_D8_DA8
PE12.Signal=FMC_D9_DA9
PE13.Signal=FMC_D10_DA10
PE14.Signal=FMC_D11_DA11
PE15.Signal=FMC_D12_DA12
PE2.GPIOParameters=GPIO_Label
PE2.GPIO_Label=DIN4
PE2.Signal=GPIO_Input
PE3.GPIOParameters=GPIO_Label
PE3.GPIO_Label=DIN3
PE3.Signal=GPIO_Input
PE4.GPIOParameters=GPIO_Label
PE4.GPIO_Label=DIN2
PE4.Signal=GPIO_Input
PE5.GPIOParameters=GPIO_Label
PE5.GPIO_Label=DIN1
PE5.Signal=S_TIM9_CH1
PE6.GPIOParameters=GPIO_Label
PE6.GPIO_Label=DIN0
PE6.Signal=S_TIM9_CH2
PE7.Signal=FMC_D4_DA4
PE8.Signal=FMC_D5_DA5
PE9.Signal=FMC_D6_DA6
PF0.Signal=FMC_A0
PF1.Signal=FMC_A1
PF10.GPIOParameters=GPIO_Label
PF10.GPIO_Label=DIB_IRQ
PF10.Signal=GPIO_Output
PF11.Signal=FMC_SDNRAS
PF12.Signal=FMC_A6
PF13.Signal=FMC_A7
PF14.Signal=FMC_A8
PF15.Signal=FMC_A9
PF2.Signal=FMC_A2
PF3.Signal=FMC_A3
PF4.Signal=FMC_A4
PF5.Signal=FMC_A5
PF6.GPIOParameters=GPIO_Label
PF6.GPIO_Label=DIN5
PF6.Signal=GPIO_Input
PF7.GPIOParameters=GPIO_Label
PF7.GPIO_Label=DIN6
PF7.Signal=GPIO_Input
PF8.GPIOParameters=GPIO_Label
PF8.GPIO_Label=DIB_SYNC
PF8.Signal=GPIO_Input
PF9.GPIOParameters=GPIO_Label
PF9.GPIO_Label=ADIB2_ID2
PF9.Signal=GPIO_Input
PG0.Signal=FMC_A10
PG1.Signal=FMC_A11
PG10.GPIOParameters=GPIO_Label
PG10.GPIO_Label=ISEL_S\#3
PG10.Signal=GPIO_Output
PG11.GPIOParameters=GPIO_Label
PG11.GPIO_Label=USEL100\#1
PG11.Signal=GPIO_Output
PG12.GPIOParameters=GPIO_Label
PG12.GPIO_Label=USEL20\#1
PG12.Signal=GPIO_Output
PG13.GPIOParameters=GPIO_Label
PG13.GPIO_Label=USEL1\#1
PG13.Signal=GPIO_Output
PG14.GPIOParameters=GPIO_Label
PG14.GPIO_Label=ISEL\#1
PG14.Signal=GPIO_Output
PG15.Signal=FMC_SDNCAS
PG2.GPIOParameters=GPIO_Label
PG2.GPIO_Label=MIO_CS0
PG2.Signal=GPIO_Output
PG3.GPIOParameters=GPIO_Label
PG3.GPIO_Label=MIO_CS1
PG3.Signal=GPIO_Output
PG4.Signal=FMC_A14_BA0
PG5.Signal=FMC_A15_BA1
PG6.GPIOParameters=GPIO_Label
PG6.GPIO_Label=AFE_ID0
PG6.Signal=GPIO_Input
PG7.GPIOParameters=GPIO_Label
PG7.GPIO_Label=AFE_ID1
PG7.Signal=GPIO_Input
PG8.Signal=FMC_SDCLK
PG9.GPIOParameters=GPIO_Label
PG9.GPIO_Label=ISEL_R\#3
PG9.Signal=GPIO_Output
PH0-OSC_IN.Mode=HSE-External-Oscillator
PH0-OSC_IN.Signal=RCC_OSC_IN
PH1-OSC_OUT.Mode=HSE-External-Oscillator
PH1-OSC_OUT.Signal=RCC_OSC_OUT
RCC.HSE_VALUE=16000000
RCC.SYSCLKFreq_VALUE=180000000
RCC.SYSCLKSource=RCC_SYSCLKSOURCE_PLLRCLK
board=custom

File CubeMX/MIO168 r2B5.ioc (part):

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PB13.GPIOParameters=GPIO_Label
PD12.GPIO_Label=ADIB1_ID1
PC7.GPIOParameters=GPIO_Label
PE11.GPIOParameters=GPIO_Label
PF14.PinState=GPIO_PIN_SET
PG8.Signal=GPIO_Output
PG0.Signal=GPXTI0
PG14.GPIOParameters=GPIO_Label
PA2.GPIOParameters=GPIO_Label
PG2.GPIOParameters=GPIO_PuPd,GPIO_Label
PG15.GPIO_Label=ADC_DRDY
PB6.Signal=GPIO_Output
PC7.Signal=GPIO_Output
PB12.PinState=GPIO_PIN_SET
PD0.Signal=GPIO_Output
PD8.Signal=GPXTI8
PE1.Signal=GPIO_Input
PB3.Mode=Full_Duplex_Master
PF1.GPIO_Label=USEL10\#2
PD1.GPIO_Label=USEL1\#3
PB12.GPIO_Label=DAC_CS_DUAL
PF12.GPIO_Label=DAC_CLR\#1
PC4.GPIO_Label=DOUT4
PE9.Signal=GPIO_Input
PG12.GPIOParameters=GPIO_Label
PB14.Mode=Full_Duplex_Master
PB1.GPIO_Label=DOUT7
PG4.GPIO_Label=IN_CTRL6
PE4.GPIO_Label=DIN2
PC9.Mode=SD_4_bits_Wide_bus
PD14.GPIO_PuPd=GPIO_PULLUP
PE13.Mode=Full_Duplex_Slave
PG0.GPIO_PuPd=GPIO_PULLUP
Mcu.Package=LQFP144
PB9.Signal=GPIO_Output
PB1.Signal=GPIO_Output
PD12.Signal=GPIO_Input
PA10.Signal=GPIO_Output
PE12.GPIO_Label=DIB_SCLK
PC11.Mode=SD_4_bits_Wide_bus
PB13.Mode=Full_Duplex_Master
PA4.GPIO_Label=DOUT_EN
PD15.Signal=GPIO_Input
PG12.Signal=GPIO_Output
PE12.Mode=Full_Duplex_Slave
PA6.GPIOParameters=GPIO_Label
PD6.GPIOParameters=GPIO_Label
PG5.Signal=GPIO_Output
PC13.Signal=GPIO_Output
PD3.Signal=GPIO_Output
PC2.Signal=GPIO_Output
PC14-OSC32_IN.Signal=GPIO_Output
PC3.GPIOParameters=GPIO_Label
PB8.GPIO_Label=SLOW_DIN\#1
PE8.GPIO_Label=AFE_ID1
PF3.GPIOParameters=GPIO_Label
PG6.GPIOParameters=GPIO_Label
PB14.Signal=SPI2_MISO
PA5.Signal=S_TIM2_CH1_ETR
PE13.GPIOParameters=GPIO_Label
PC12.Mode=SD_4_bits_Wide_bus
PE1.GPIO_Label=DIN5
PE14.Signal=SPI4_MOSI
PB4.GPIO_Label=ADC_MISO
PB15.GPIO_Label=DAC_MOSI
PG15.GPIO_ModeDefaultEXTI=GPIO_MODE_IT_FALLING
PG7.GPIO_Label=IN_CTRL3
PF4.GPIO_Label=ISEL_R\#4
PA1.GPIO_Label=DOUT1
PF13.Signal=GPIO_Output
PC7.GPIO_Label=IN_CTRL0
PC8.Mode=SD_4_bits_Wide_bus
PD14.GPIOParameters=GPIO_PuPd,GPIO_Label
PA5.GPIO_Label=PWM1
PE5.GPIO_Label=DIN1
PF0.GPIO_Label=USEL1\#2
PG0.GPIOParameters=GPIO_PuPd,GPIO_Label
PD0.GPIOParameters=GPIO_Label
PE3.Signal=GPIO_Input
PF4.Signal=GPIO_Output
PD2.Signal=SDIO_CMD
PB10.PinState=GPIO_PIN_SET
PG9.GPIOParameters=GPIO_Label
PG2.Signal=GPIO_Input
PE11.GPIO_Label=DIB_NSS
PF0.GPIOParameters=GPIO_Label
PA12.GPIOParameters=GPIO_PuPd,GPIO_Label
PD0.GPIO_Label=USEL10\#3
PB13.GPIO_Label=DAC_SCK
PD8.GPIO_PuPd=GPIO_PULLUP
PG5.GPIO_Label=IN_CTRL5
PB15.Signal=SPI2_MOSI
PF12.GPIOParameters=GPIO_Label
PG11.Signal=GPIO_Output
PG15.Signal=GPXTI15
PB5.GPIOParameters=GPIO_Label
PD13.Signal=GPIO_Input
PA15.GPIO_Label=ADC_CS
PE4.GPIOParameters=GPIO_Label
PF1.GPIOParameters=GPIO_Label
PF13.GPIO_Speed=GPIO_SPEED_FREQ_VERY_HIGH
PG8.GPIOParameters=GPIO_Label
PA0-WKUP.GPIOParameters=GPIO_Speed,GPIO_Label
RCC.HSE_VALUE=16000000
PA0-WKUP.GPIO_Speed=GPIO_SPEED_FREQ_LOW
PA14.Mode=Serial_Wire
PF11.Signal=GPIO_Output
PB5.Mode=Full_Duplex_Master
PE3.GPIOParameters=GPIO_Label
PB7.Signal=GPIO_Output
PF11.GPIOParameters=PinState,GPIO_Label
PB6.GPIOParameters=GPIO_Label
PH1-OSC_OUT.Mode=HSE-External-Oscillator
PB7.GPIO_Label=ADC_CLK
PD13.GPIO_Label=ADIB1_ID0
PA6.Signal=GPIO_Input
PD5.GPIO_Label=ISEL_LOW\#3
PG1.GPIO_PuPd=GPIO_PULLUP
PA15.Signal=GPIO_Output
PG0.GPIO_Label=DAC_CLR-SEL\#2
PB5.GPIO_Label=ADC_MOSI
PG11.GPIO_Label=USEL100\#1
PC5.Signal=GPIO_Output
PD3.GPIO_Label=ADIB1_SW
PE7.Signal=GPIO_Output
PD6.Signal=GPIO_Output
PF3.GPIO_Label=ISEL_S\#4
PF15.GPIOParameters=GPIO_Label
PE2.GPIO_Label=DIN4
PB4.Signal=SPI3_MISO
PG2.GPIO_Label=ADIB2_ID0
PA3.Signal=GPIO_Output
PD15.GPIO_Label=ADIB2_ID1
PB8.GPIOParameters=GPIO_Label
PG7.Signal=GPIO_Output
PE14.GPIOParameters=GPIO_Label
PC11.Signal=SDIO_D3
PC8.Signal=SDIO_D0
PC10.Mode=SD_4_bits_Wide_bus
PE14.GPIO_Label=DIB_MOSI
PA12.GPIO_Label=SD_DETECT
PE15.GPIOParameters=GPIO_Label
PD8.GPIO_Label=DAC_ALARM
PB9.GPIOParameters=GPIO_Label
PG8.GPIO_Label=IN_CTRL2
PA13.Signal=SYS_JTMS-SWDIO
PB10.GPIO_Label=DIB_IRQ
PB7.GPIOParameters=PinState,GPIO_Label
PC5.GPIOParameters=GPIO_Label
PE2.GPIOParameters=GPIO_Label
PG10.GPIOParameters=GPIO_Label
PA1.Signal=GPIO_Output
PD2.Mode=SD_4_bits_Wide_bus
board=custom
PF14.GPIOParameters=PinState,GPIO_Label
PB15.Mode=Full_Duplex_Master
PA15.PinState=GPIO_PIN_SET
PC1.GPIO_Label=ISEL10_R\#4
PA10.GPIOParameters=GPIO_Label
PD4.GPIOParameters=GPIO_Label
PF15.GPIO_Label=DAC_CLR\#2
PF1.Signal=GPIO_Output
PE0.Signal=GPIO_Input
PE7.GPIO_Label=BIAS_EN
PE12.Signal=SPI4_SCK
RCC.SYSCLKFreq_VALUE=180000000
PA15.GPIO_Speed=GPIO_SPEED_FREQ_LOW
PF13.GPIOParameters=GPIO_Speed,PinState,GPIO_Label
PC6.GPIOParameters=GPIO_Label
PB12.Signal=GPIO_Output
PG11.GPIOParameters=GPIO_Label
PE1.GPIOParameters=GPIO_Label
PA3.GPIO_Label=DOUT3
PH0-OSC_IN.Signal=RCC_OSC_IN
PG2.GPIO_PuPd=GPIO_PULLUP
PG4.Signal=GPIO_Output
PC12.Signal=SDIO_CK
PB14.GPIO_Label=DAC_MISO
PG6.GPIO_Label=IN_CTRL4
PG3.GPIOParameters=GPIO_Label
PE8.GPIO_PuPd=GPIO_PULLUP
PD3.GPIOParameters=GPIO_Label
PC6.GPIO_Label=IN_CTRL1
PA3.GPIOParameters=GPIO_Label
PA6.GPIO_Label=DIN7
PB6.GPIO_Label=ADC_START
PB13.Signal=SPI2_SCK
PD6.GPIO_Label=ISEL10_R\#3
PG13.Signal=GPIO_Output
PC15-OSC32_OUT.GPIO_Label=ISEL\#2
PE6.GPIO_Label=DIN0
RCC.SYSCLKSource=RCC_SYSCLKSOURCE_PLLCLK
PD15.GPIOParameters=GPIO_PuPd,GPIO_Label
PD4.Signal=GPIO_Output
PC3.Signal=GPIO_Output
PE5.Signal=S_TIM9_CH1
PD1.GPIOParameters=GPIO_Label
PG1.GPIOParameters=GPIO_PuPd,GPIO_Label
PB0.GPIOParameters=GPIO_Label
PE0.GPIOParameters=GPIO_Label
PA1.GPIOParameters=GPIO_Label
PE2.Signal=GPIO_Input
PF3.Signal=GPIO_Output
PB7.PinState=GPIO_PIN_SET
PG13.GPIOParameters=GPIO_Label
PG5.GPIOParameters=GPIO_Label
PD5.GPIOParameters=GPIO_Label
PA5.GPIOParameters=GPIO_Label
PB14.GPIOParameters=GPIO_Label
PF14.Signal=GPIO_Output
PB10.GPIOParameters=PinState,GPIO_Label
PC15-OSC32_OUT.GPIOParameters=GPIO_Label
PA12.GPIO_PuPd=GPIO_PULLUP
PC4.GPIOParameters=GPIO_Label
PF4.GPIOParameters=GPIO_Label
PA15.GPIOParameters=GPIO_Speed,PinState,GPIO_Label
PG9.Signal=GPIO_Output
PC6.Signal=GPIO_Output
PD13.GPIOParameters=GPIO_PuPd,GPIO_Label
PD7.Signal=GPIO_Output
PD1.Signal=GPIO_Output
PF14.GPIO_Label=DAC_CS\#2
PF13.PinState=GPIO_PIN_SET
PF13.GPIO_Label=DAC_CLR-SEL\#1
PG13.GPIO_Label=USEL1\#1
PA0-WKUP.GPIO_Label=DOUT0
PA0-WKUP.Signal=GPIO_Output
PG10.Signal=GPIO_Output
PE9.GPIO_Label=AFE_ID0
PB10.Signal=GPIO_Output
PF2.GPIOParameters=GPIO_Label
PE15.Signal=GPIO_Input
PE8.Signal=GPIO_Input
PC2.GPIOParameters=GPIO_Label
PA13.Mode=Serial_Wire
PG14.GPIO_Label=ISEL\#1
PA4.Signal=GPIO_Output
PB5.Signal=SPI3_MOSI
PG15.GPIOParameters=GPIO_PuPd,GPIO_Label,GPIO_ModeDefaultEXTI
PE13.GPIO_Label=DIB_MISO
PD11.Signal=GPIO_Input
PC3.GPIO_Label=ISEL_MID\#4
PE12.GPIOParameters=GPIO_Label
PG3.GPIO_Label=IN_CTRL7
PB0.Signal=GPIO_Output
PA7.GPIOParameters=GPIO_Label
PC1.Signal=GPIO_Output
PB12.GPIOParameters=PinState,GPIO_Label
PG15.GPIO_PuPd=GPIO_PULLUP
PG10.GPIO_Label=ISEL_S\#3
PD7.GPIOParameters=GPIO_Label
PG7.GPIOParameters=GPIO_Label
PG6.Signal=GPIO_Output
Mcu.UserName=STM32F446ZCTx
PC10.Signal=SDIO_D2
PB0.GPIO_Label=DOUT6
PC13.GPIO_Label=USEL1\#4
PE5.GPIOParameters=GPIO_Label
PD11.GPIO_PuPd=GPIO_PULLUP
PB4.GPIOParameters=GPIO_Label
PA12.Signal=GPIO_Input
PE11.Mode=NSS_Signal_Hard_Input
PC1.GPIOParameters=GPIO_Label
PD11.GPIO_Label=ADIB1_ID2
PF11.GPIO_Label=DAC_CS\#1
PD8.GPIOParameters=GPIO_PuPd,GPIO_Label
PF12.Signal=GPIO_Output
PH0-OSC_IN.Mode=HSE-External-Oscillator
PB4.Mode=Full_Duplex_Master
PE13.Signal=SPI4_MISO
PA10.GPIO_Label=ADIB2_SW
PF11.PinState=GPIO_PIN_SET
PB3.GPIOParameters=GPIO_Label
PE4.Signal=GPIO_Input
PE6.GPIOParameters=GPIO_Label
PC14-OSC32_IN.GPIOParameters=GPIO_Label
PD7.GPIO_Label=ISEL10_S\#3
PA2.GPIO_Label=DOUT2
PD15.GPIO_PuPd=GPIO_PULLUP
PF5.GPIO_Label=ISEL10_S\#4
PE0.GPIO_Label=DIN6
PF5.Signal=GPIO_Output
PC14-OSC32_IN.GPIO_Label=USEL10\#4
PF0.Signal=GPIO_Output
PC2.GPIO_Label=ISEL_LOW\#4
PB3.GPIO_Label=ADC_SCK
PE8.GPIOParameters=GPIO_PuPd,GPIO_Label
PB9.GPIO_Label=SLOW_DIN\#0
PG3.Signal=GPIO_Output
PG1.Signal=GPIO_Input
PC4.Signal=GPIO_Output
PD5.Signal=GPIO_Output
PE9.GPIOParameters=GPIO_PuPd,GPIO_Label
PE15.GPIO_Label=DIB_SYNC
PD12.GPIOParameters=GPIO_PuPd,GPIO_Label
PE7.GPIOParameters=GPIO_Label
PF2.Signal=GPIO_Output
PF5.GPIOParameters=GPIO_Label
PE11.Signal=SPI4_NSS
PC15-OSC32_OUT.Signal=GPIO_Output
PG9.GPIO_Label=ISEL_R\#3
PG14.Signal=GPIO_Output
PG1.GPIO_Label=DOUT_FAULT
PD11.GPIOParameters=GPIO_PuPd,GPIO_Label
PG4.GPIOParameters=GPIO_Label
PC13.GPIOParameters=GPIO_Label
PD4.GPIO_Label=ISEL_MID\#3
PE14.Mode=Full_Duplex_Slave
PH1-OSC_OUT.Signal=RCC_OSC_OUT
PD13.GPIO_PuPd=GPIO_PULLUP
PF15.Signal=GPIO_Output
PD14.GPIO_Label=ADIB2_ID2
PA4.GPIOParameters=GPIO_Label
PE6.Signal=S_TIM9_CH2
PB15.GPIOParameters=GPIO_Label
Mcu.Name=STM32F446Z(C-E)Tx
PA2.Signal=GPIO_Output
PD14.Signal=GPIO_Input
PB3.Signal=SPI3_SCK
PA7.GPIO_Label=PWM2
PC5.GPIO_Label=DOUT5
PA14.Signal=SYS_JTCK-SWCLK
PG12.GPIO_Label=USEL10\#1
PB8.Signal=GPIO_Output
PE3.GPIO_Label=DIN3
PC9.Signal=SDIO_D1
PD12.GPIO_PuPd=GPIO_PULLUP
PB1.GPIOParameters=GPIO_Label
PA7.Signal=S_TIM3_CH2
PE9.GPIO_PuPd=GPIO_PULLUP
PF2.GPIO_Label=USEL100\#2
